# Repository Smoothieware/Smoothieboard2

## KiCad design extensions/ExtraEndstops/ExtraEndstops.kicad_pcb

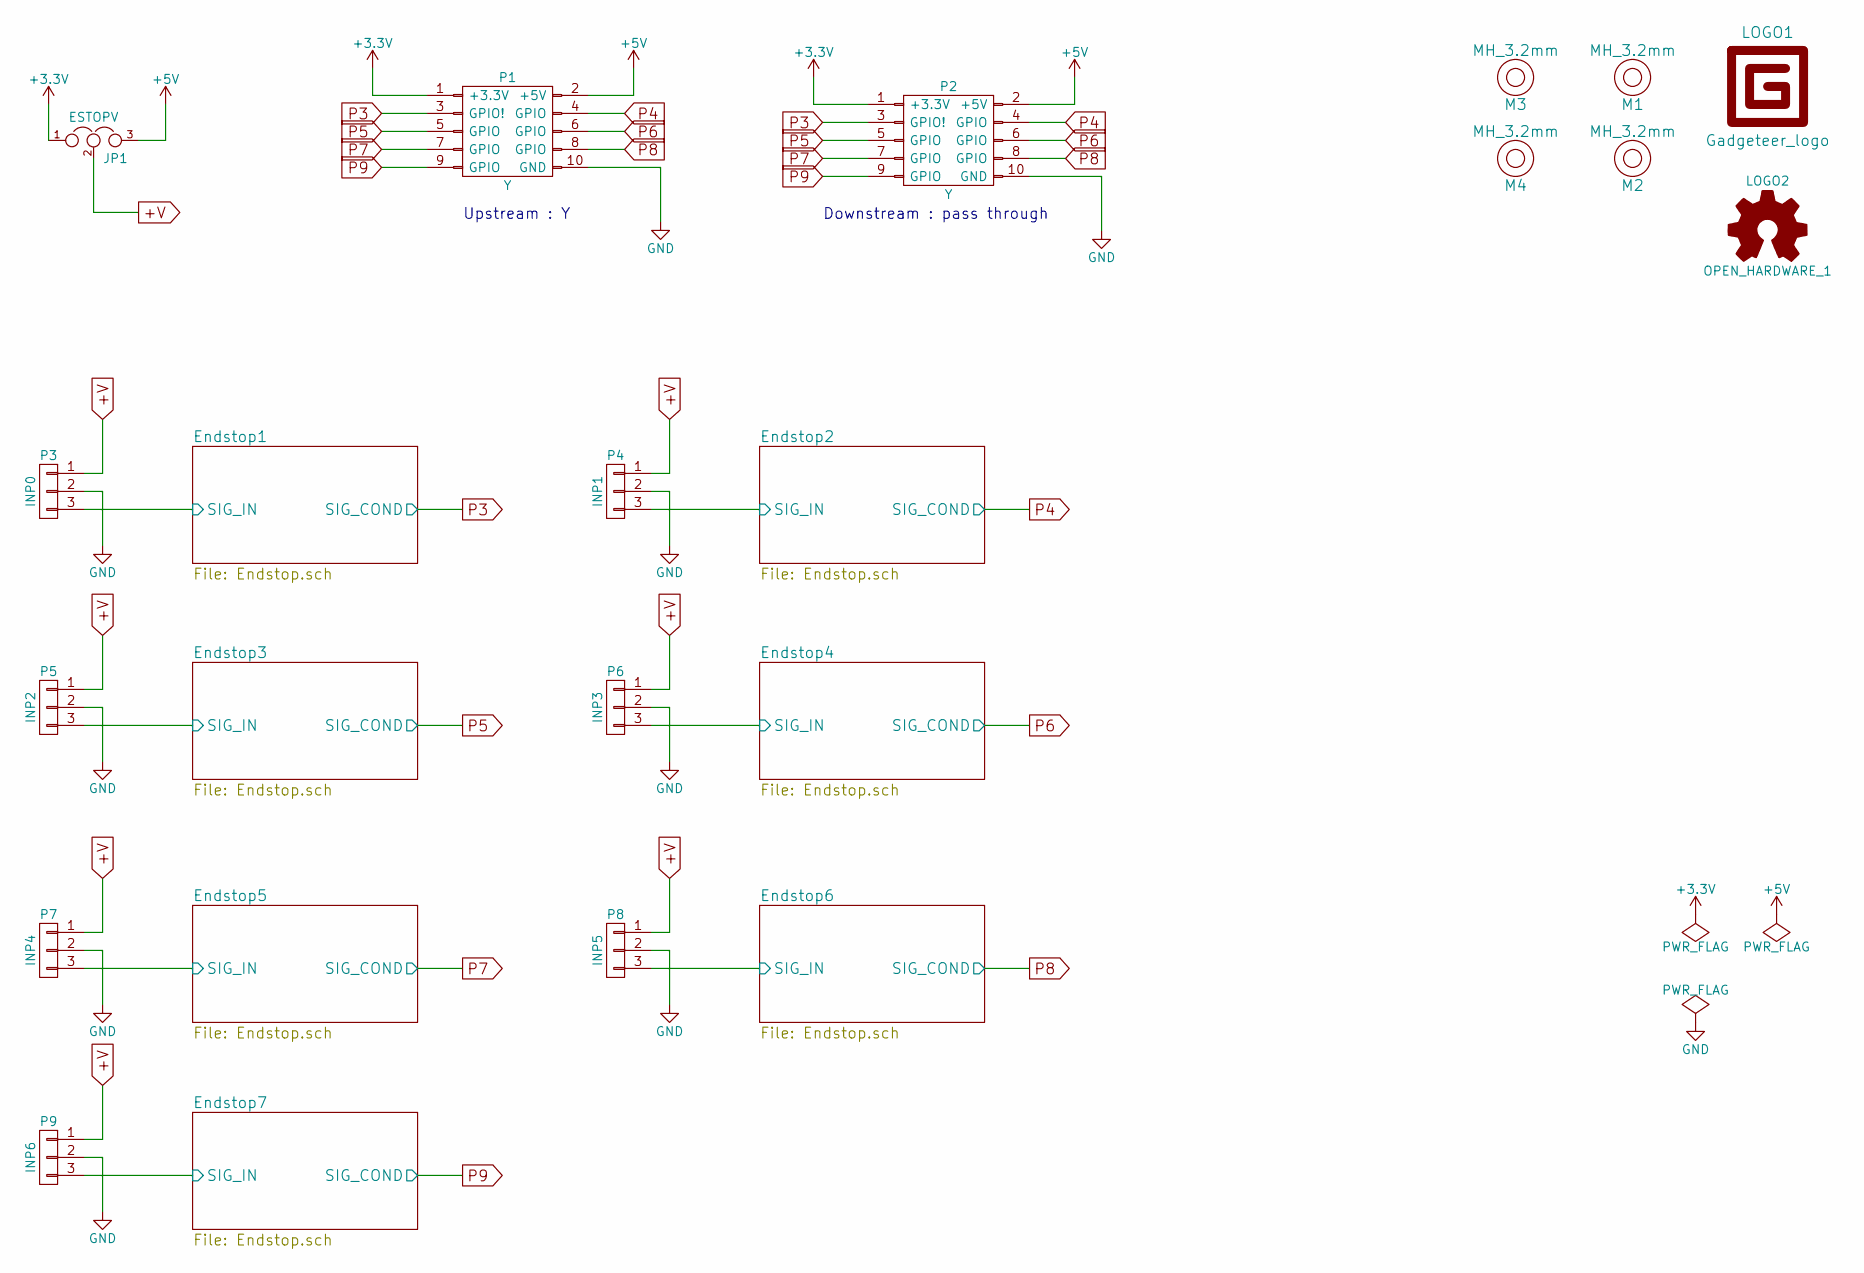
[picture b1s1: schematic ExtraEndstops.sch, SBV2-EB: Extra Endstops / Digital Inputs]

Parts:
JP1: ESTOPV; Pin_Header_Straight_1x03
LOGO1: Gadgeteer_logo
LOGO2: OPEN_HARDWARE_1; Logo_silk_OSHW_12x13mm
M1, M2, M3, M4: MH_3.2mm; M3_Mounting_Hole
P1, P2: Y; SHF-105-01-L-D-SM-LC
P3: INP0; Hdr_MOLEX-KK-RM2-54mm_Lock_3pin_straight
P4: INP1; Hdr_MOLEX-KK-RM2-54mm_Lock_3pin_straight
P5: INP2; Hdr_MOLEX-KK-RM2-54mm_Lock_3pin_straight
P6: INP3; Hdr_MOLEX-KK-RM2-54mm_Lock_3pin_straight
P7: INP4; Hdr_MOLEX-KK-RM2-54mm_Lock_3pin_straight
P8: INP5; Hdr_MOLEX-KK-RM2-54mm_Lock_3pin_straight
P9: INP6; Hdr_MOLEX-KK-RM2-54mm_Lock_3pin_straight

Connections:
+3V3: JP1.1, P1.1 (+3.3V), P2.1 (+3.3V); also elsewhere on the board
+5V: JP1.3, P1.2 (+5V), P2.2 (+5V)
+V: JP1.2, P3.1, P4.1, P5.1, P6.1, P7.1, P8.1, P9.1; also elsewhere on the board
/Endstop1/SIG_IN: P3.3; also elsewhere on the board
/Endstop2/SIG_IN: P4.3; also elsewhere on the board
/Endstop3/SIG_IN: P5.3; also elsewhere on the board
/Endstop4/SIG_IN: P6.3; also elsewhere on the board
/Endstop5/SIG_IN: P7.3; also elsewhere on the board
/Endstop6/SIG_IN: P8.3; also elsewhere on the board
/Endstop7/SIG_IN: P9.3; also elsewhere on the board
GND: P1.10 (GND), P2.10 (GND), P3.2, P4.2, P5.2, P6.2, P7.2, P8.2, P9.2; also elsewhere on the board
P3: P1.3 (GPIO!), P2.3 (GPIO!); also elsewhere on the board
P4: P1.4 (GPIO), P2.4 (GPIO); also elsewhere on the board
P5: P1.5 (GPIO), P2.5 (GPIO); also elsewhere on the board
P6: P1.6 (GPIO), P2.6 (GPIO); also elsewhere on the board
P7: P1.7 (GPIO), P2.7 (GPIO); also elsewhere on the board
P8: P1.8 (GPIO), P2.8 (GPIO); also elsewhere on the board
P9: P1.9 (GPIO), P2.9 (GPIO); also elsewhere on the board

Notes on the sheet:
Upstream : Y
Downstream : pass through

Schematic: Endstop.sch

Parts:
C1: 100n; C_0603
D1: LED; LED-0603
D2: 1N4148WS; SOD-323
JP2: Bridge; SB_0603
R1: 680; R_0603
R2: 1k; R_0603
R3: 5k6; R_0603

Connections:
+3V3: R1.1; also elsewhere on the board
+V: R2.1; also elsewhere on the board
/Endstop1/SIG_IN: D2.1; also elsewhere on the board
GND: C1.2; also elsewhere on the board
unnamed: C1.1, JP2.1, R3.1
unnamed: D1.1 (K), D2.2, R2.2, R3.2
unnamed: D1.2 (A), R1.2
P3: JP2.2; also elsewhere on the board

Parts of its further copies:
C2, C3, C4, C5, C6, C7: 100n; C_0603
D3, D5, D7, D9, D11, D13: LED; LED-0603
D4, D6, D8, D10, D12, D14: 1N4148WS; SOD-323
JP3, JP4, JP5, JP6, JP7, JP8: Bridge; SB_0603
R4, R7, R10, R13, R16, R19: 680; R_0603
R5, R8, R11, R14, R17, R20: 1k; R_0603
R6, R9, R12, R15, R18, R21: 5k6; R_0603

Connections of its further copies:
+3V3: R4.1, R7.1, R10.1, R13.1, R16.1, R19.1; also elsewhere on the board
+V: R5.1, R8.1, R11.1, R14.1, R17.1, R20.1; also elsewhere on the board
/Endstop2/SIG_IN: D4.1; also elsewhere on the board
/Endstop3/SIG_IN: D6.1; also elsewhere on the board
/Endstop4/SIG_IN: D8.1; also elsewhere on the board
/Endstop5/SIG_IN: D10.1; also elsewhere on the board
/Endstop6/SIG_IN: D12.1; also elsewhere on the board
/Endstop7/SIG_IN: D14.1; also elsewhere on the board
GND: C2.2, C3.2, C4.2, C5.2, C6.2, C7.2; also elsewhere on the board
unnamed: C2.1, JP3.1, R6.1
unnamed: C3.1, JP4.1, R9.1
unnamed: C4.1, JP5.1, R12.1
unnamed: C5.1, JP6.1, R15.1
unnamed: C6.1, JP7.1, R18.1
unnamed: C7.1, JP8.1, R21.1
unnamed: D3.1 (K), D4.2, R5.2, R6.2
unnamed: D3.2 (A), R4.2
unnamed: D5.1 (K), D6.2, R8.2, R9.2
unnamed: D5.2 (A), R7.2
unnamed: D7.1 (K), D8.2, R11.2, R12.2
unnamed: D7.2 (A), R10.2
unnamed: D9.2 (A), R13.2
unnamed: D9.1 (K), D10.2, R14.2, R15.2
unnamed: D11.1 (K), D12.2, R17.2, R18.2
unnamed: D11.2 (A), R16.2
unnamed: D13.1 (K), D14.2, R20.2, R21.2
unnamed: D13.2 (A), R19.2
P4: JP3.2; also elsewhere on the board
P5: JP4.2; also elsewhere on the board
P6: JP5.2; also elsewhere on the board
P7: JP6.2; also elsewhere on the board
P8: JP7.2; also elsewhere on the board
P9: JP8.2; also elsewhere on the board

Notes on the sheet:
LED on when SIG_IN is low
Cut jumper to isolate input

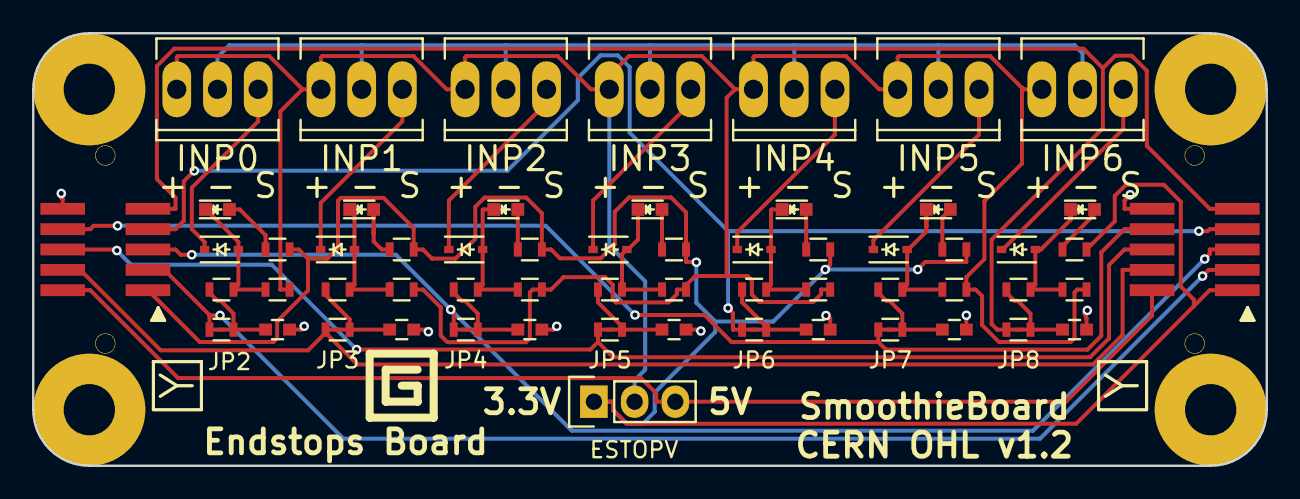
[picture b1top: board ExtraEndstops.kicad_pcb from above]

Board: 2 copper layers, 77.0 x 27.0 mm, 65 parts (1 on the bottom side), 39 nets.

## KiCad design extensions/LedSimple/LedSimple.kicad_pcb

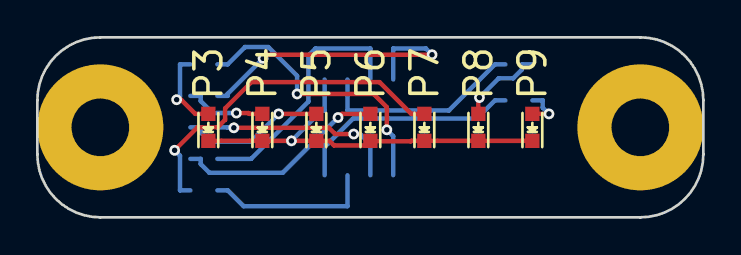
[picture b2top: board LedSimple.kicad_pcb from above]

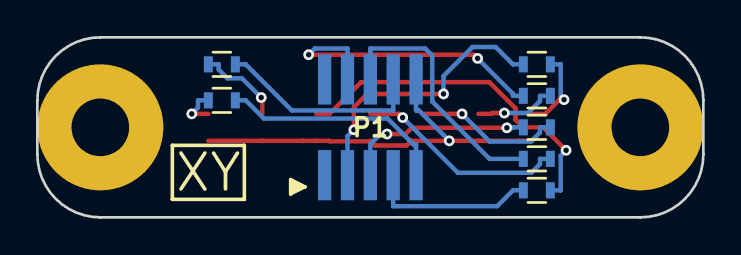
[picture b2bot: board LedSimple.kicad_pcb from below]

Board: 2 copper layers, 37.0 x 10.0 mm, 17 parts (8 on the bottom side), 15 nets.

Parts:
D1: P3; LED-0603
D2: P4; LED-0603
D3: P5; LED-0603
D4: P6; LED-0603
D5: P7; LED-0603
D6: P8; LED-0603
D7: P9; LED-0603
M1, M2: MH_3.2mm; M3_Mounting_Hole
P1: XY; SHF-105-01-L-D-SM
R1, R2, R3, R4, R5, R6, R7: 330; R_0603

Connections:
/P3: P1.3, R1.2
/P4: P1.4, R2.2
/P5: P1.5, R3.2
/P6: P1.6, R4.2
/P7: P1.7, R5.2
/P8: P1.8, R6.2
/P9: P1.9, R7.2
GND: D1.1, D2.1, D3.1, D4.1, D5.1, D6.1, D7.1, P1.10
unnamed: D1.2, R1.1
unnamed: D2.2, R2.1
unnamed: D3.2, R3.1
unnamed: D4.2, R4.1
unnamed: D5.2, R5.1
unnamed: D6.2, R6.1
unnamed: D7.2, R7.1

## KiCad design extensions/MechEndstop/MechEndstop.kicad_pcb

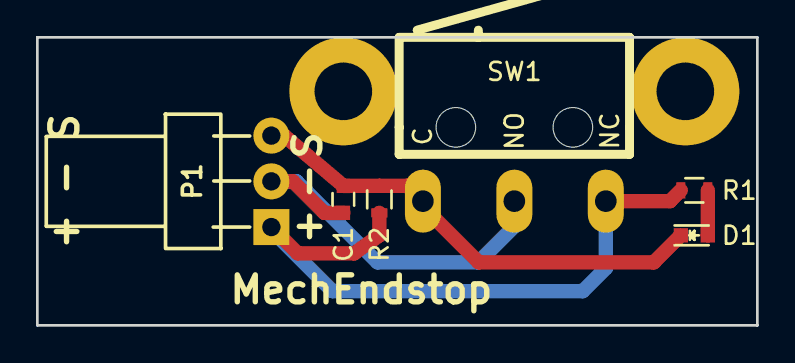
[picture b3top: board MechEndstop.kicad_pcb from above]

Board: 2 copper layers, 40.0 x 16.0 mm, 9 parts (1 on the bottom side), 4 nets.

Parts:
C1: 100n; C_0603
D1: LED; LED-0603
LOGO1: OPEN_HARDWARE_1; Logo_silk_OSHW_12x13mm
M1, M2: MH_3.2mm; M3_Mounting_Hole
P1: CONN_01X03; CONN_KK_2.54_3W_RA
R1: 1k; R_0603
R2: 10k; R_0603
SW1: Microswitch; Omron-D2F-A

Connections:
/~SIG: C1.1, D1.1, P1.3, R2.2, SW1.1
GND: C1.2, P1.2, SW1.2
unnamed: D1.2, R1.2
VCC: P1.1, R1.1, R2.1, SW1.3

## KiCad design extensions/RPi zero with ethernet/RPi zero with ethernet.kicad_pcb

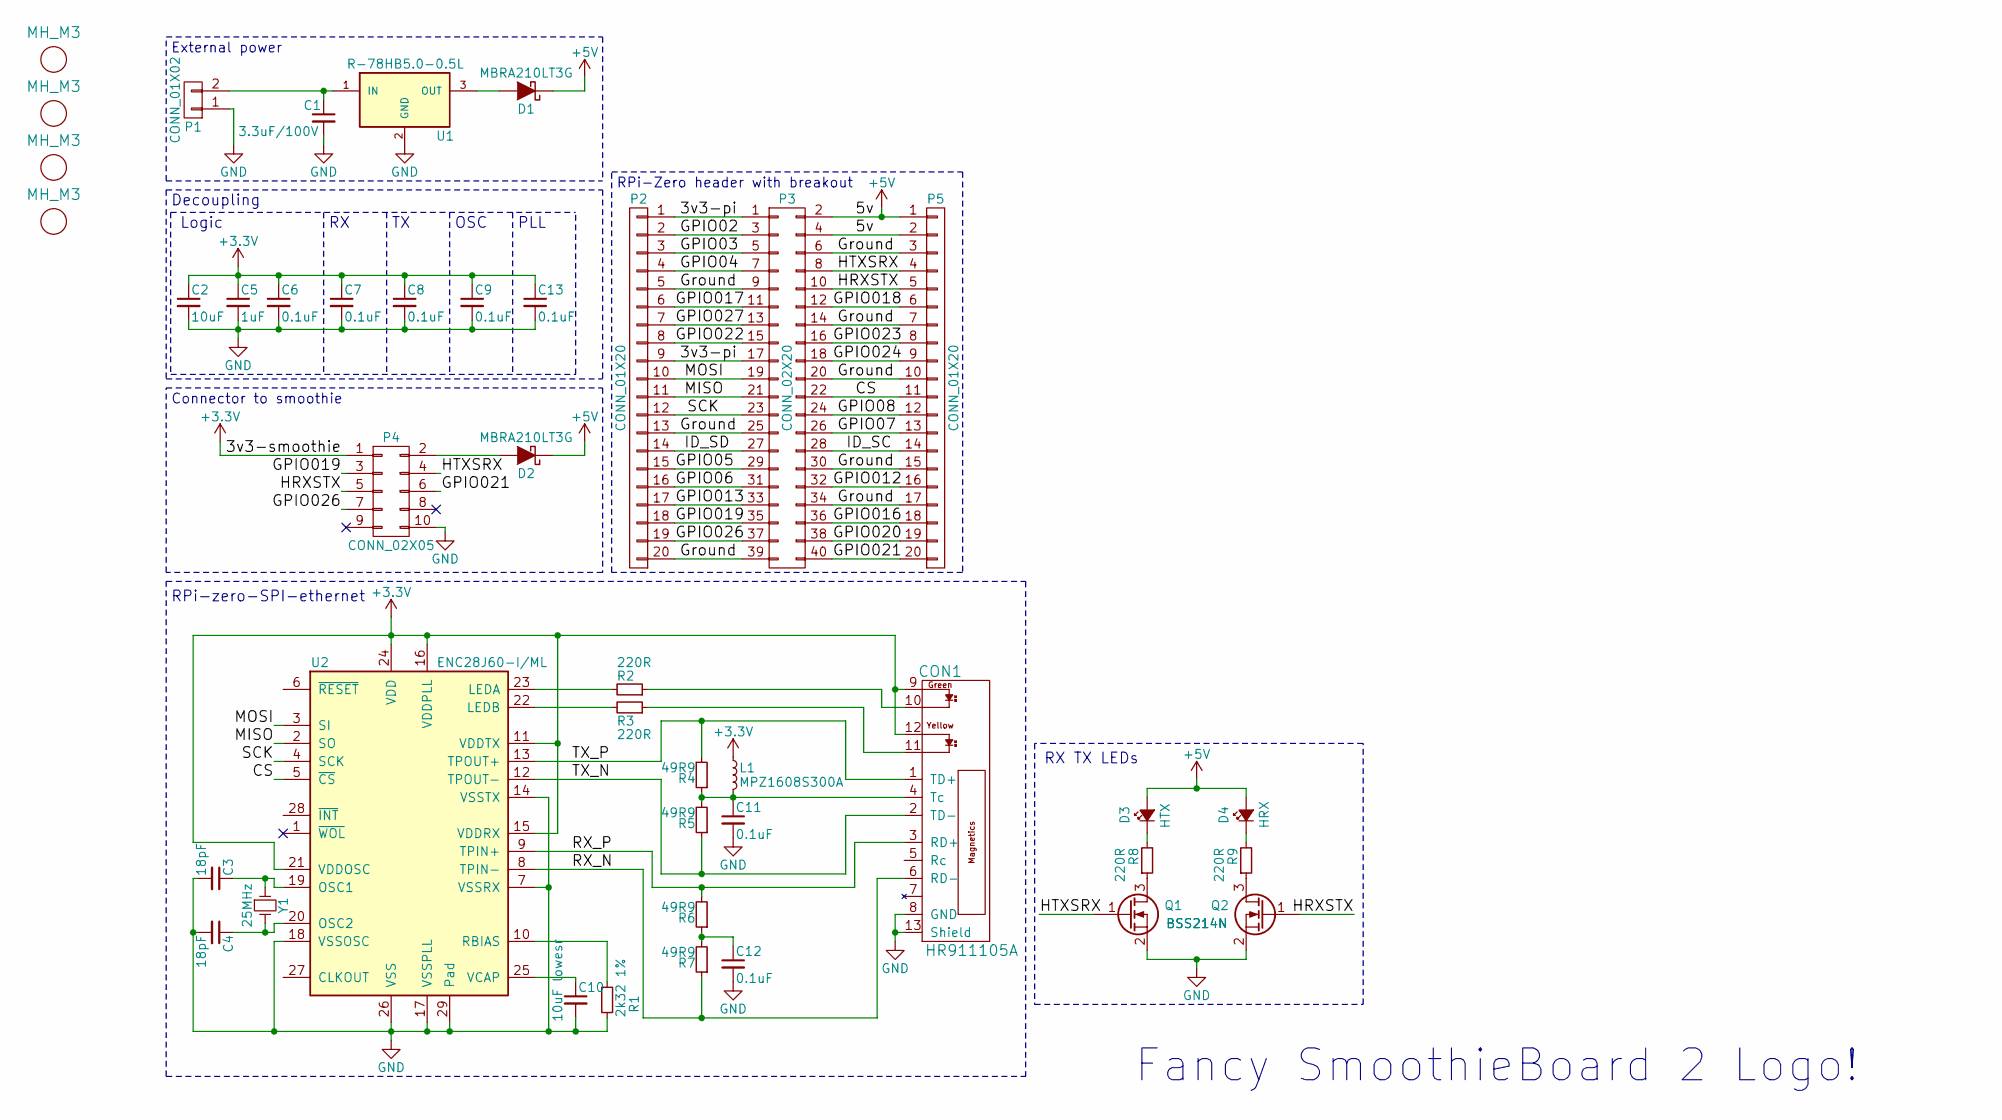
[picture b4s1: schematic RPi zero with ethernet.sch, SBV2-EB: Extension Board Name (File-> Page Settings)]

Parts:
C1: 3.3uF/100V; C_1206
C2: 10uF; C_0603
C3, C4: 18pF; C_0603
C5: 1uF; C_0603
C6, C7, C8, C9, C11, C12, C13: 0.1uF; C_0603
C10: 10uF lowesr; C_0603
CON1: HR911105A
D1, D2: MBRA210LT3G; SMA_Standard
D3: HTX; D_0805
D4: HRX; D_0805
L1: MPZ1608S300A; R_0603
M1, M2, M3, M4: MH_M3; MountingHole_3.2mm_M3; Digikey Part No. ND
P1: CONN_01X02; FCI_20020110-C021A01LF
P2, P5: CONN_01X20; Pin_Header_Straight_1x20_Pitch2.54mm
P3: CONN_02X20; Pin_Header_Straight_2x20_Pitch2.54mm
P4: CONN_02X05; SHF-105-01-L-D-SM-LC
Q1, Q2: BSS214N; SOT-23
R1: 2k32 1%; R_0603
R2, R3, R8, R9: 220R; R_0603
R4, R5, R6, R7: 49R9; R_0603
U1: R-78HB5.0-0.5L; R-78HBx.x-x.xL
U2: ENC28J60-I/ML; QFN-28-1EP_6x6mm_Pitch0.65mm
Y1: 25MHz; Crystal_SMD_HC49-SD

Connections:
+3V3: C2.1, C5.1, C6.1, C7.1, C8.1, C9.1, C13.1, CON1.9, CON1.12, L1.1, P4.1, U2.11 (VDDTX), U2.15 (VDDRX), U2.16 (VDDPLL), U2.21 (VDDOSC), U2.24 (VDD)
+5V: D1.1 (K), D2.1 (K), D3.2 (A), D4.2 (A), P3.2, P3.4, P5.1, P5.2
/3v3-pi: P2.1, P2.9, P3.1, P3.17
/CS: P3.22, P5.11, U2.5 (~CS)
/GPIO02: P2.2, P3.3
/GPIO03: P2.3, P3.5
/GPIO04: P2.4, P3.7
/GPIO05: P2.15, P3.29
/GPIO06: P2.16, P3.31
/GPIO07: P3.26, P5.13
/GPIO08: P3.24, P5.12
/GPIO012: P3.32, P5.16
/GPIO013: P2.17, P3.33
/GPIO016: P3.36, P5.18
/GPIO017: P2.6, P3.11
/GPIO018: P3.12, P5.6
/GPIO019: P2.18, P3.35, P4.3
/GPIO020: P3.38, P5.19
/GPIO021: P3.40, P4.6, P5.20
/GPIO022: P2.8, P3.15
/GPIO023: P3.16, P5.8
/GPIO024: P3.18, P5.9
/GPIO026: P2.19, P3.37, P4.7
/GPIO027: P2.7, P3.13
/Ground: P2.5, P2.13, P2.20, P3.6, P3.9, P3.14, P3.20, P3.25, P3.30, P3.34, P3.39, P5.3, P5.7, P5.10, P5.15, P5.17
/HRXSTX: P3.10, P4.5, P5.5, Q2.1 (G)
/HTXSRX: P3.8, P4.4, P5.4, Q1.1 (G)
/ID_SC: P3.28, P5.14
/ID_SD: P2.14, P3.27
/MISO: P2.11, P3.21, U2.2 (SO)
/MOSI: P2.10, P3.19, U2.3 (SI)
/RX_N: CON1.6 (RD-), R7.1, U2.8 (TPIN-)
/RX_P: CON1.3 (RD+), R6.2, U2.9 (TPIN+)
/SCK: P2.12, P3.23, U2.4 (SCK)
/TX_N: CON1.2 (TD-), R5.1, U2.12 (TPOUT-)
/TX_P: CON1.1 (TD+), R4.2, U2.13 (TPOUT+)
GND: C1.2, C2.2, C3.2, C4.2, C5.2, C6.2, C7.2, C8.2, C9.2, C10.2, C11.2, C12.2, C13.2, CON1.8 (GND), CON1.13 (Shield), P1.1, P4.10, Q1.2 (S), Q2.2 (S), R1.2, U1.2 (GND), U2.7 (VSSRX), U2.14 (VSSTX), U2.17 (VSSPLL), U2.18 (VSSOSC), U2.26 (VSS), U2.29 (Pad)
unnamed: C1.1, P1.2, U1.1 (IN)
unnamed: C3.1, U2.19 (OSC1), Y1.1
unnamed: C4.1, U2.20 (OSC2), Y1.2
unnamed: C10.1, U2.25 (VCAP)
unnamed: C11.1, CON1.4 (Tc), L1.2, R4.1, R5.2
unnamed: C12.1, R6.1, R7.2
unnamed: CON1.10, R2.1
unnamed: CON1.11, R3.1
unnamed: D1.2 (A), U1.3 (OUT)
unnamed: D2.2 (A), P4.2
unnamed: D3.1 (K), R8.2
unnamed: D4.1 (K), R9.2
unnamed: Q1.3 (D), R8.1
unnamed: Q2.3 (D), R9.1
unnamed: R1.1, U2.10 (RBIAS)
unnamed: R2.2, U2.23 (LEDA)
unnamed: R3.2, U2.22 (LEDB)

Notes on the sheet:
Fancy SmoothieBoard 2 Logo!
External power
Connector to smoothie
RPi-Zero header with breakout
RPi-zero-SPI-ethernet
OSC
Logic
Decoupling
PLL
RX TX LEDs

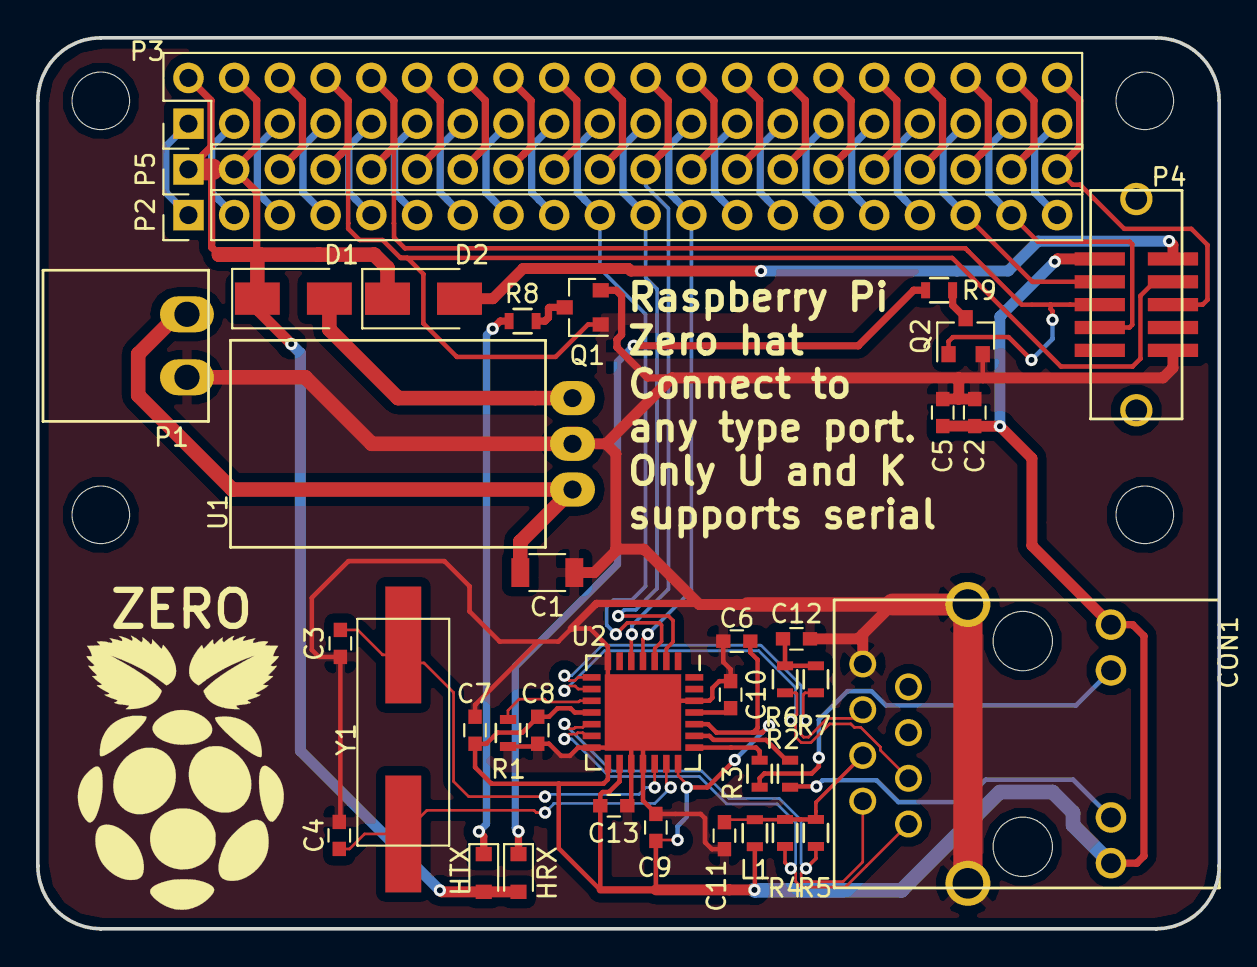
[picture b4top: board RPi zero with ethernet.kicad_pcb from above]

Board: 2 copper layers, 65.6 x 49.5 mm, 42 parts (0 on the bottom side), 54 nets.

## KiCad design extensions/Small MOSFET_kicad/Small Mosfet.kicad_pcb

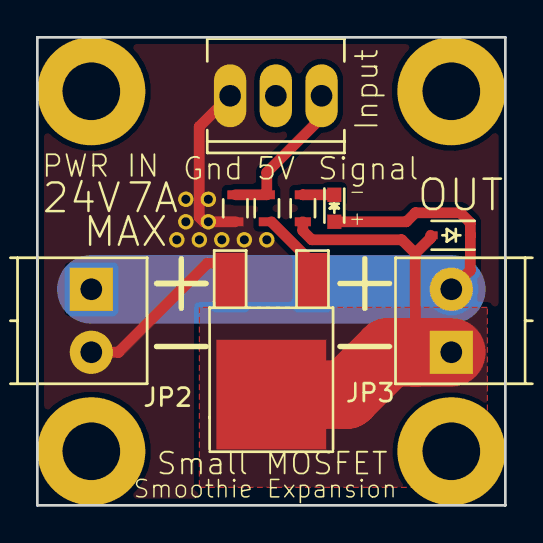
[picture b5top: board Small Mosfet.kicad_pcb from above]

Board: 2 copper layers, 26.0 x 26.0 mm, 22 parts (0 on the bottom side), 6 nets.

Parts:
D11: 1N4148; SOD-323
JP1: Hdr_MOLEX-KK-RM2-54mm_Lock_3pin_straight
JP2, JP3: TerminalBlock_Pheonix_PT-3.5mm_2pol
LED7: LED; LED-0603
M1, M2, M3, M4: MH_3.2mm; M3_Mounting_Hole
Q1: IRLR024; TO-252-2Lead
R35: 10R; R_0603
R36: 100k; R_0603
R37: 1.5k; R_0603
VP1, VP2, VP3, VP4, VP5, VP6, VP7, VP8, VP9: VIA_GND; VIA_GND_0.86mm

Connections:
/E1-CONTROL: D11.2, JP3.1, Q1.2, R37.1
/FET-LOGIC-IN: JP1.3, R35.2, R36.1
/HEATERVIN: D11.1, JP2.1, JP3.2, LED7.2
GND: JP1.1, JP2.2, Q1.3, R36.2, VP1.1, VP2.1, VP3.1, VP4.1, VP5.1, VP6.1, VP7.1, VP8.1, VP9.1
unnamed: LED7.1, R37.2
unnamed: Q1.1, R35.1

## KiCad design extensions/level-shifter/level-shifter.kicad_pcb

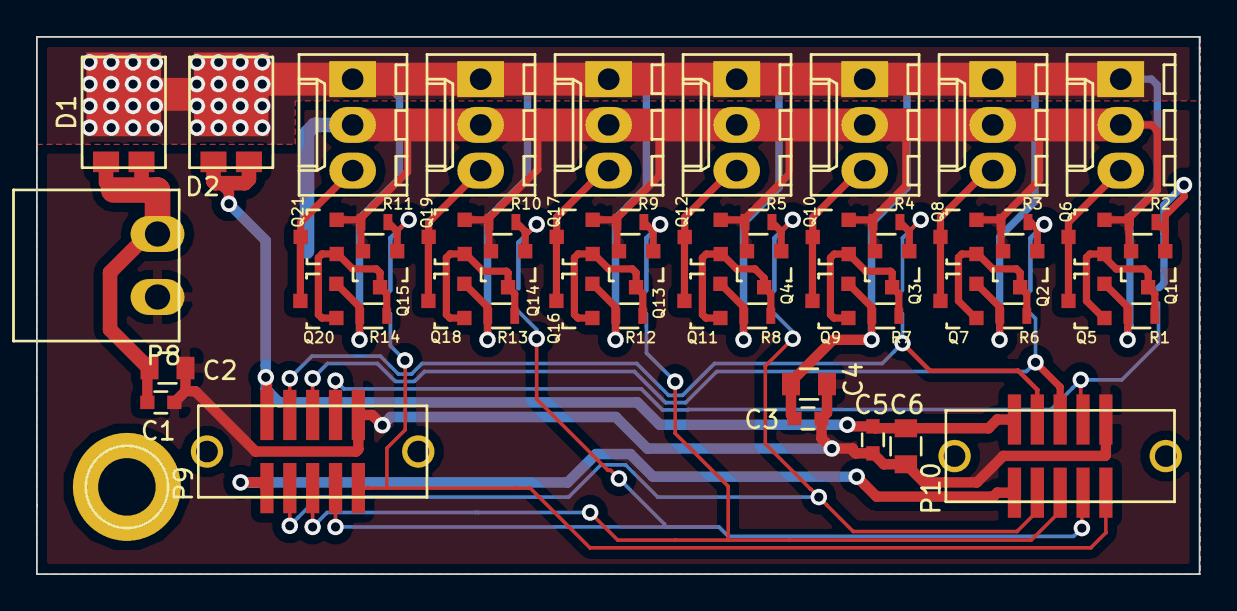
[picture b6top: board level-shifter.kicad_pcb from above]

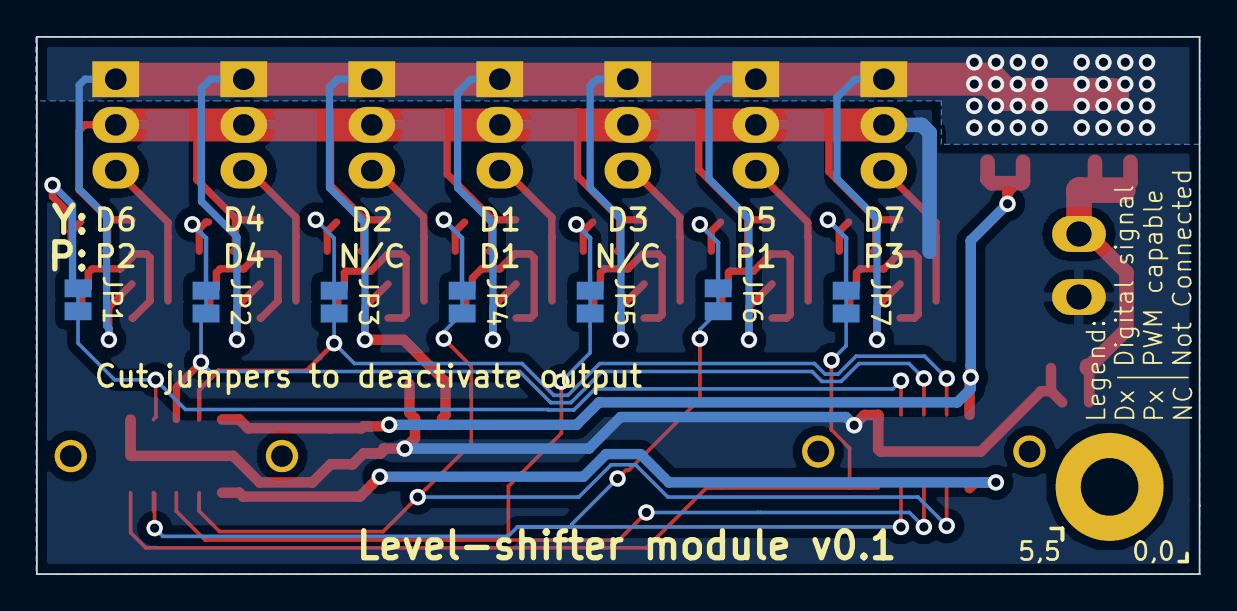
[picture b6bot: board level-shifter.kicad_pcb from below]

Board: 2 copper layers, 64.6 x 29.8 mm, 61 parts (7 on the bottom side), 33 nets.

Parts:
5,5: 1pin
C1, C3, C5: 100nF; C_0603
C2, C4, C6: 10uF; C_0805
D1, D2: FSV12120V; TO-277_3L
JP1, JP2, JP3, JP4, JP5, JP6, JP7: JUMPER; Solder-jumper-NC
P1, P2, P3, P4, P5, P6, P7: CONN_01X03; Molex_KK_6410-03
P8: CONN_01X02; FCI_20020110-C021A01LF
P9, P10: CONN_02X05; SHF-105-01-L-D-SM-LC
Q1, Q2, Q3, Q4, Q6, Q8, Q10, Q12, Q13, Q14, Q15, Q17, Q19, Q21: FDN339AN; SOT-23
Q5, Q7, Q9, Q11, Q16, Q18, Q20: SI2301; SOT-23
R1, R2, R3, R4, R5, R6, R7, R8, R9, R10, R11, R12, R13, R14: 1K; R_0603

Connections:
+3V3: P9.1, P10.1
+5V: C5.1, C6.1, D2.2, P9.2, P10.2
GND: C1.2, C2.2, C3.2, C4.2, C5.2, C6.2, P1.2, P2.2, P3.2, P4.2, P5.2, P6.2, P7.2, P8.1, P9.10, P10.10, Q1.2, Q2.2, Q3.2, Q4.2, Q6.2, Q8.2, Q10.2, Q12.2, Q13.2, Q14.2, Q15.2, Q17.2, Q19.2, Q21.2, R2.2, R3.2, R4.2, R5.2, R9.2, R10.2, R11.2
GPIO1: JP4.1, P9.3, P10.3
GPIO2: JP3.1, P9.4, P10.4
GPIO3: JP5.1, P9.5, P10.5
GPIO4: JP2.1, P9.6, P10.6
GPIO5: JP6.1, P9.7, P10.7
GPIO6: JP1.1, P9.8, P10.8
GPIO7: JP7.1, P9.9, P10.9
unnamed: JP1.2, Q1.1, R2.1
unnamed: JP2.2, Q2.1, R3.1
unnamed: JP3.2, Q3.1, R4.1
unnamed: JP4.2, Q4.1, R5.1
unnamed: JP5.2, Q13.1, R9.1
unnamed: JP6.2, Q14.1, R10.1
unnamed: JP7.2, Q15.1, R11.1
unnamed: P1.3, Q5.3, Q6.3
unnamed: P2.3, Q7.3, Q8.3
unnamed: P3.3, Q9.3, Q10.3
unnamed: P4.3, Q11.3, Q12.3
unnamed: P5.3, Q16.3, Q17.3
unnamed: P6.3, Q18.3, Q19.3
unnamed: P7.3, Q20.3, Q21.3
unnamed: Q1.3, Q5.1, Q6.1, R1.2
unnamed: Q2.3, Q7.1, Q8.1, R6.2
unnamed: Q3.3, Q9.1, Q10.1, R7.2
unnamed: Q4.3, Q11.1, Q12.1, R8.2
unnamed: Q13.3, Q16.1, Q17.1, R12.2
unnamed: Q14.3, Q18.1, Q19.1, R13.2
unnamed: Q15.3, Q20.1, Q21.1, R14.2
VDD: C3.1, C4.1, D1.1, D2.1, P1.1, P2.1, P3.1, P4.1, P5.1, P6.1, P7.1, Q5.2, Q7.2, Q9.2, Q11.2, Q16.2, Q18.2, Q20.2, R1.1, R6.1, R7.1, R8.1, R12.1, R13.1, R14.1
VPP: C1.1, C2.1, D1.2, P8.2

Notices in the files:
extensions/ExtraEndstops/ExtraEndstops.kicad_pcb:
CERN OHL v1.2
extensions/ExtraEndstops/ExtraEndstops.sch:
CERN OHL 1.2
